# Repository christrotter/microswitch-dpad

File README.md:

# microswitch-dpad
What if your dpad could have leds?  But also fit in a tiny area?

This is that.

# Features
- 4x addressable LEDs via DI/DO pins
- 4x Omron B3U-1000P (_no diodes; pinned as 1x shared on input side, 4x output sides e.g. 1x row, 4x col_)
  - 150gf switches cuz who reads and comprehends datasheets anyways

# dpad-inator inatoring

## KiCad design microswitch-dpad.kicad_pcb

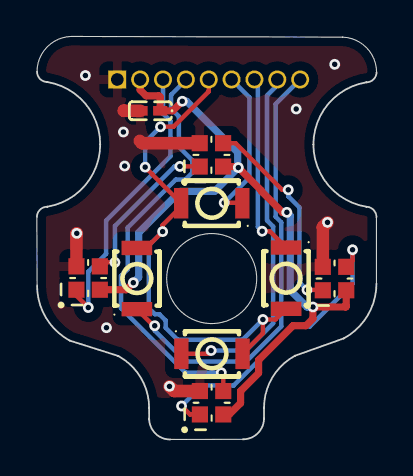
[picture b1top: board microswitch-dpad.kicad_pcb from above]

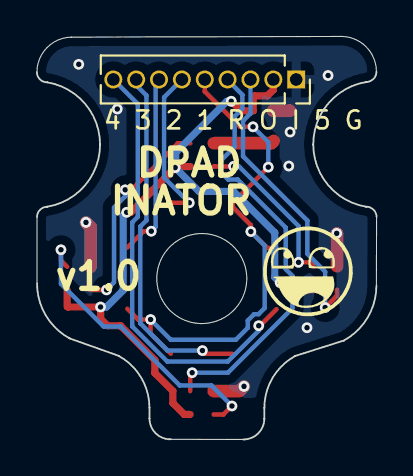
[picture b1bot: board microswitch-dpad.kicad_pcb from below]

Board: 2 copper layers, 18.9 x 22.4 mm, 11 parts (2 on the bottom side), 12 nets.

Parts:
C1: C0402X7R104K160NTB; C0402
D1, D2, D3, D4: SK6805-EC15; LED_dilemma_SK6805-EC15_1.5x1.5mm_P0.6mm_handsolder
J1: Conn_01x09_Socket; PinSocket_1x09_P1.27mm_Vertical
LOGO2: **REF; awesome-logo
U1, U2, U3, U4: D2LS-21_C3823622; KEY-SMD_B3U-1000PM

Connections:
+5V: C1.1, D1.2 (VDD), D2.2 (VDD), D3.2 (VDD), D4.2 (VDD), J1.2
DI: D1.1 (DIN), J1.3
DO: D4.3 (DOUT), J1.4
GND: C1.2, D1.4 (GND), D2.4 (GND), D3.4 (GND), D4.4 (GND), J1.1
unnamed: D1.3 (DOUT), D2.1 (DIN)
unnamed: D2.3 (DOUT), D3.1 (DIN)
unnamed: D3.3 (DOUT), D4.1 (DIN)
col1: J1.6, U1.1
col2: J1.7, U2.1
col3: J1.8, U3.1
col4: J1.9, U4.1
row: J1.5, U1.2, U2.2, U3.2, U4.2

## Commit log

2024-04-10 adding first draft pcb
2024-04-10 added in do, fixed some traces
2024-04-11 about to change up the wiring...
2024-04-12 production submitted
2024-04-28 adding readme and images
